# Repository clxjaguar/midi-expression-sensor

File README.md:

# midi-expression-sensor
MIDI Expression Sensor (Add your breath into your play!)

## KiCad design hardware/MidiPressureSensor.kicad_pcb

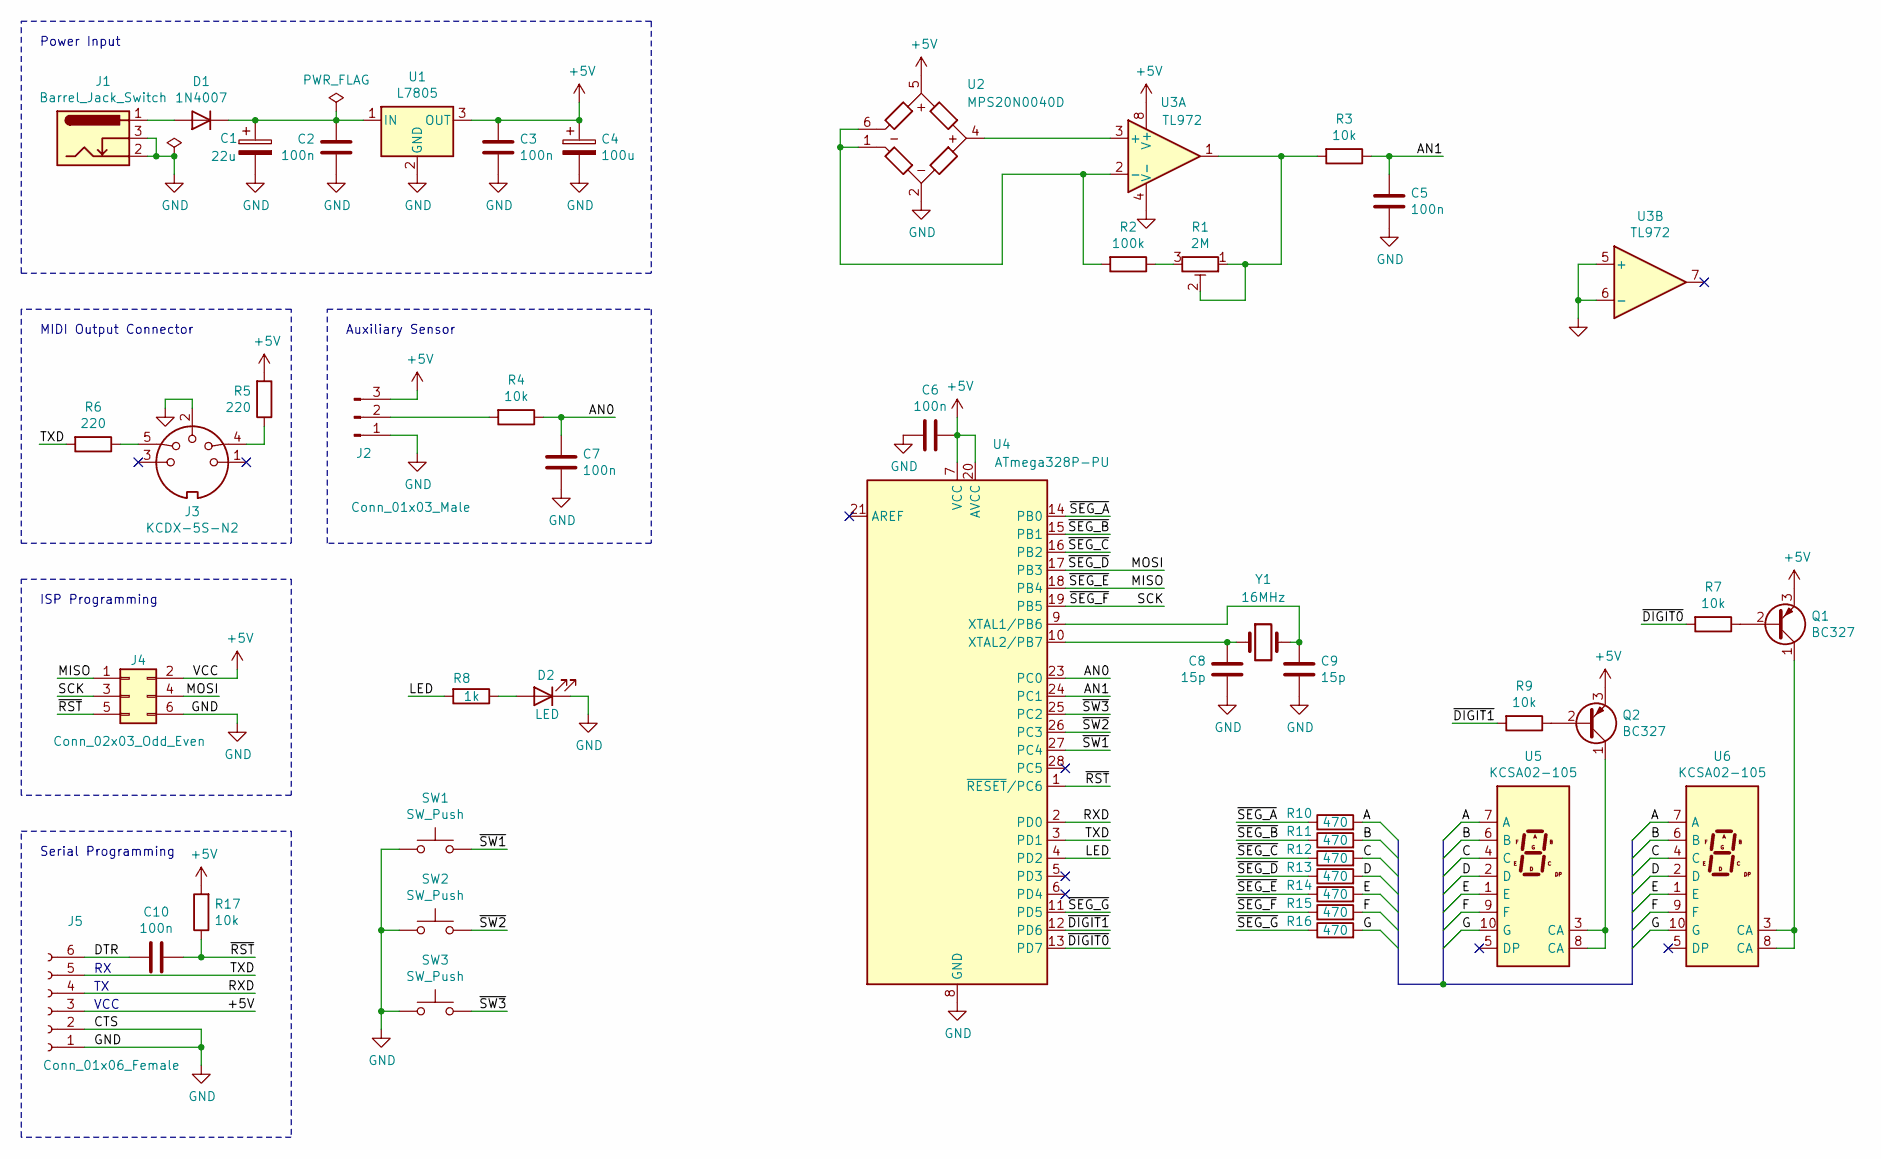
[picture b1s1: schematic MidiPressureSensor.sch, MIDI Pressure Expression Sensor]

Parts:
C1: 22u; CP_Radial_D8.0mm_P5.00mm
C2, C3, C5, C6, C7, C10: 100n; C_Rect_L7.0mm_W2.5mm_P5.00mm
C4: 100u; CP_Radial_D8.0mm_P5.00mm
C8, C9: 15p; C_Disc_D4.3mm_W1.9mm_P5.00mm
D1: 1N4007; D_DO-41_SOD81_P10.16mm_Horizontal
D2: LED; LED_D3.0mm
J1: Barrel_Jack_Switch; BARREL_JACK
J2: Conn_01x03_Male; Pin_Header_Angled_1x03_Pitch2.54mm
J3: KCDX-5S-N2
J4: Conn_02x03_Odd_Even; Pin_Header_Straight_2x03_Pitch2.54mm
J5: Conn_01x06_Female; Pin_Header_Straight_1x06_Pitch2.54mm
Q1, Q2: BC327; TO-92_Inline_Wide
R1: 2M; Potentiometer_Trimmer_Piher_PT-10v10_Horizontal_Px10.0mm_Py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
R2: 100k; R_Axial_DIN0207_L6.3mm_D2.5mm_P7.62mm_Horizontal
R3, R4, R7, R9, R17: 10k; R_Axial_DIN0207_L6.3mm_D2.5mm_P7.62mm_Horizontal
R5, R6: 220; R_Axial_DIN0207_L6.3mm_D2.5mm_P7.62mm_Horizontal
R8: 1k; R_Axial_DIN0207_L6.3mm_D2.5mm_P7.62mm_Horizontal
R10, R11, R12, R13, R14, R15, R16: 470; R_Axial_DIN0207_L6.3mm_D2.5mm_P7.62mm_Horizontal
SW1, SW2, SW3: SW_Push; SW_TH_Tactile_Omron_B3F-10xx
U1: L7805; TO-92_Inline_Wide
U2: MPS20N0040D
U3: TL972; DIP-8_W7.62mm_Socket_LongPads
U4: ATmega328P-PU; DIP-28_W7.62mm_Socket_LongPads
U5, U6: KCSA02-105; 7SegmentLED_LTS6760_LTS6780
Y1: 16MHz; Crystal_HC49-4H_Vertical

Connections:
+5V: C3.1, C4.1, C6.1, J2.3, J4.2, J5.3, Q1.3 (E), Q2.3 (E), R5.2, R17.2, U1.3 (OUT), U2.5, U3.8 (V+), U4.7 (VCC), U4.20 (AVCC)
/A: R10.2, U5.7 (A), U6.7 (A)
/AN0: C7.1, R4.1, U4.23 (PC0)
/AN1: C5.1, R3.1, U4.24 (PC1)
/B: R11.2, U5.6 (B), U6.6 (B)
/C: R12.2, U5.4 (C), U6.4 (C)
/D: R13.2, U5.2 (D), U6.2 (D)
/DTR: C10.2, J5.6
/E: R14.2, U5.1 (E), U6.1 (E)
/F: R15.2, U5.9 (F), U6.9 (F)
/G: R16.2, U5.10 (G), U6.10 (G)
/LED: R8.2, U4.4 (PD2)
/MISO: J4.1, R14.1, U4.18 (PB4)
/MOSI: J4.4, R13.1, U4.17 (PB3)
/RXD: J5.4, U4.2 (PD0)
/SCK: J4.3, R15.1, U4.19 (PB5)
/TXD: J5.5, R6.2, U4.3 (PD1)
/~DIGIT0: R7.2, U4.13 (PD7)
/~DIGIT1: R9.2, U4.12 (PD6)
/~RST: C10.1, J4.5, R17.1, U4.1 (~RESET~/PC6)
/~SEG_A: R10.1, U4.14 (PB0)
/~SEG_B: R11.1, U4.15 (PB1)
/~SEG_C: R12.1, U4.16 (PB2)
/~SEG_G: R16.1, U4.11 (PD5)
/~SW1: SW1.2, U4.27 (PC4)
/~SW2: SW2.2, U4.26 (PC3)
/~SW3: SW3.2, U4.25 (PC2)
GND: C1.2, C2.1, C3.2, C4.2, C5.2, C6.2, C7.2, C8.1, C9.2, D2.1 (K), J1.2, J1.3, J2.1, J3.2, J4.6, J5.1, J5.2, SW1.1, SW2.1, SW3.1, U1.2 (GND), U2.2, U3.4 (V-), U3.5 (+), U3.6 (-), U4.8 (GND), U4.22 (GND)
unnamed: C1.1, C2.2, D1.1 (K), U1.1 (IN)
unnamed: C8.2, U4.10 (XTAL2/PB7), Y1.1
unnamed: C9.1, U4.9 (XTAL1/PB6), Y1.2
unnamed: D1.2 (A), J1.1
unnamed: D2.2 (A), R8.1
unnamed: J2.2, R4.2
unnamed: J3.4, R5.1
unnamed: J3.5, R6.1
unnamed: Q1.1 (C), U6.3 (CA), U6.8 (CA)
unnamed: Q1.2 (B), R7.1
unnamed: Q2.1 (C), U5.3 (CA), U5.8 (CA)
unnamed: Q2.2 (B), R9.1
unnamed: R1.1, R1.2, R3.2, U3.1
unnamed: R1.3, R2.1
unnamed: R2.2, U2.1, U2.6, U3.2 (-)
unnamed: U2.4, U3.3 (+)

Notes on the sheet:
Serial Programming
ISP Programming
MIDI Output Connector
Power Input
Auxiliary Sensor
VCC

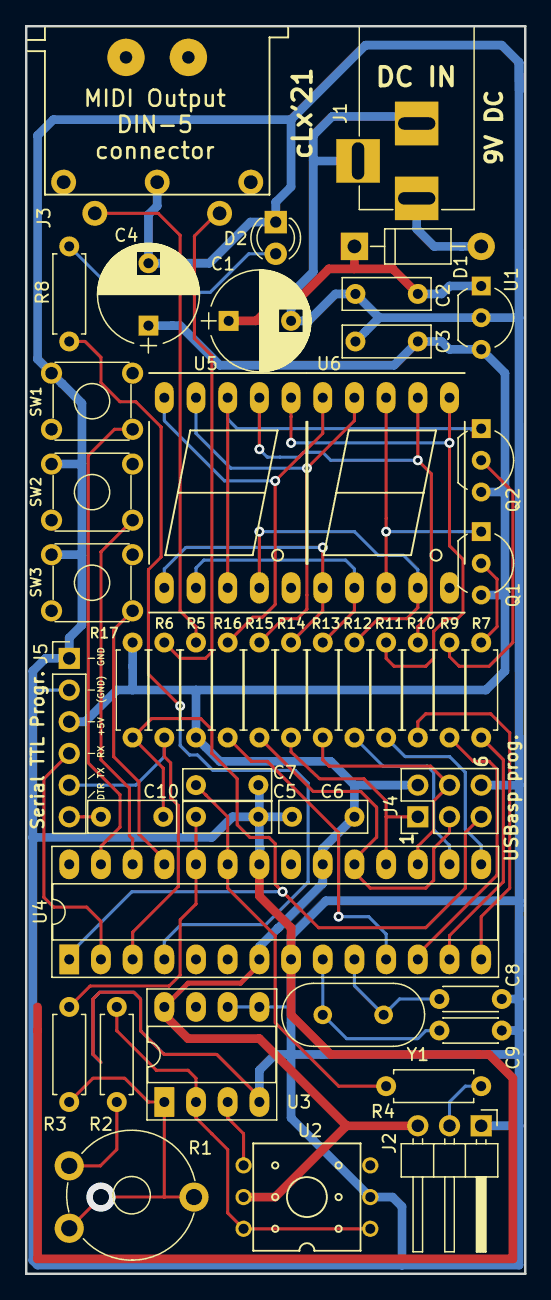
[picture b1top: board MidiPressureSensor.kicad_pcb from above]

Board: 2 copper layers, 40.0 x 100.0 mm, 46 parts (0 on the bottom side), 44 nets.

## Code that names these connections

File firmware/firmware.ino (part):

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
#include <EEPROM.h>

const int ledPin       = 2; // PD2
const int segGPin      = 5; // PD5
const int selDigit1Pin = 6; // PD6
const int selDigit0Pin = 7; // PD7
const int sw3Pin      = 16; // PC2
const int sw2Pin      = 17; // PC3
const int sw1Pin      = 18; // PC4
const int analogInPin = A1; // Analog input pin that the potentiometer is attached to

#define delay_ms delay
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
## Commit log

2023-05-25 kicad files v1 (initial release)
2023-05-25 firmware in working state (initial commit)
